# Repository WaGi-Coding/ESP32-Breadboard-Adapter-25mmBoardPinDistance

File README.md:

# ESP32-Breadboard-Adapter 25mm Board Pin Distance

Breadboard Adapter PCB to better fit an ESP32 DevKit onto your Breadboard. Has a Slot for a LED on GPIO2 and an OLED Screen (128x64).
The Pin Sequence is the same as from the ESP itself, just 2 Ground Pins got removed to save space.

It's designed for the "AZ-Delivery ESP32 DevKit C v4". If you have another Board, check the Pin mid distance, it should be 25mm, also check the Pinout of the mentioned Board.

You can DIRECTLY [ORDER FROM AISLER.NET HERE](https://aisler.net/p/QFYZRXHC) for very cheap. Here is also a 10€ Coupon Code (works atm [Jul. 10th 2022]): uCnet
You can also upload the files to some other PCB Manufacturer for sure.

### You need:
 - 2x 18Pin Male Header
 - 2x 19Pin Female Header (Hard to find, i cut 40 Pin Headers because they are cheap and easy to get)
 - (optional) I2C OLED Module (128x64 or something fitting ^^) [GND, 5V, SCL, SDA]
 - (optional) A LED (5mm or smaller diameter) + Resistor Connected to GPIO2

Made with KiCad

PS: It's a 1.6mm thick, 4 Layer PCB with throughhole Vias

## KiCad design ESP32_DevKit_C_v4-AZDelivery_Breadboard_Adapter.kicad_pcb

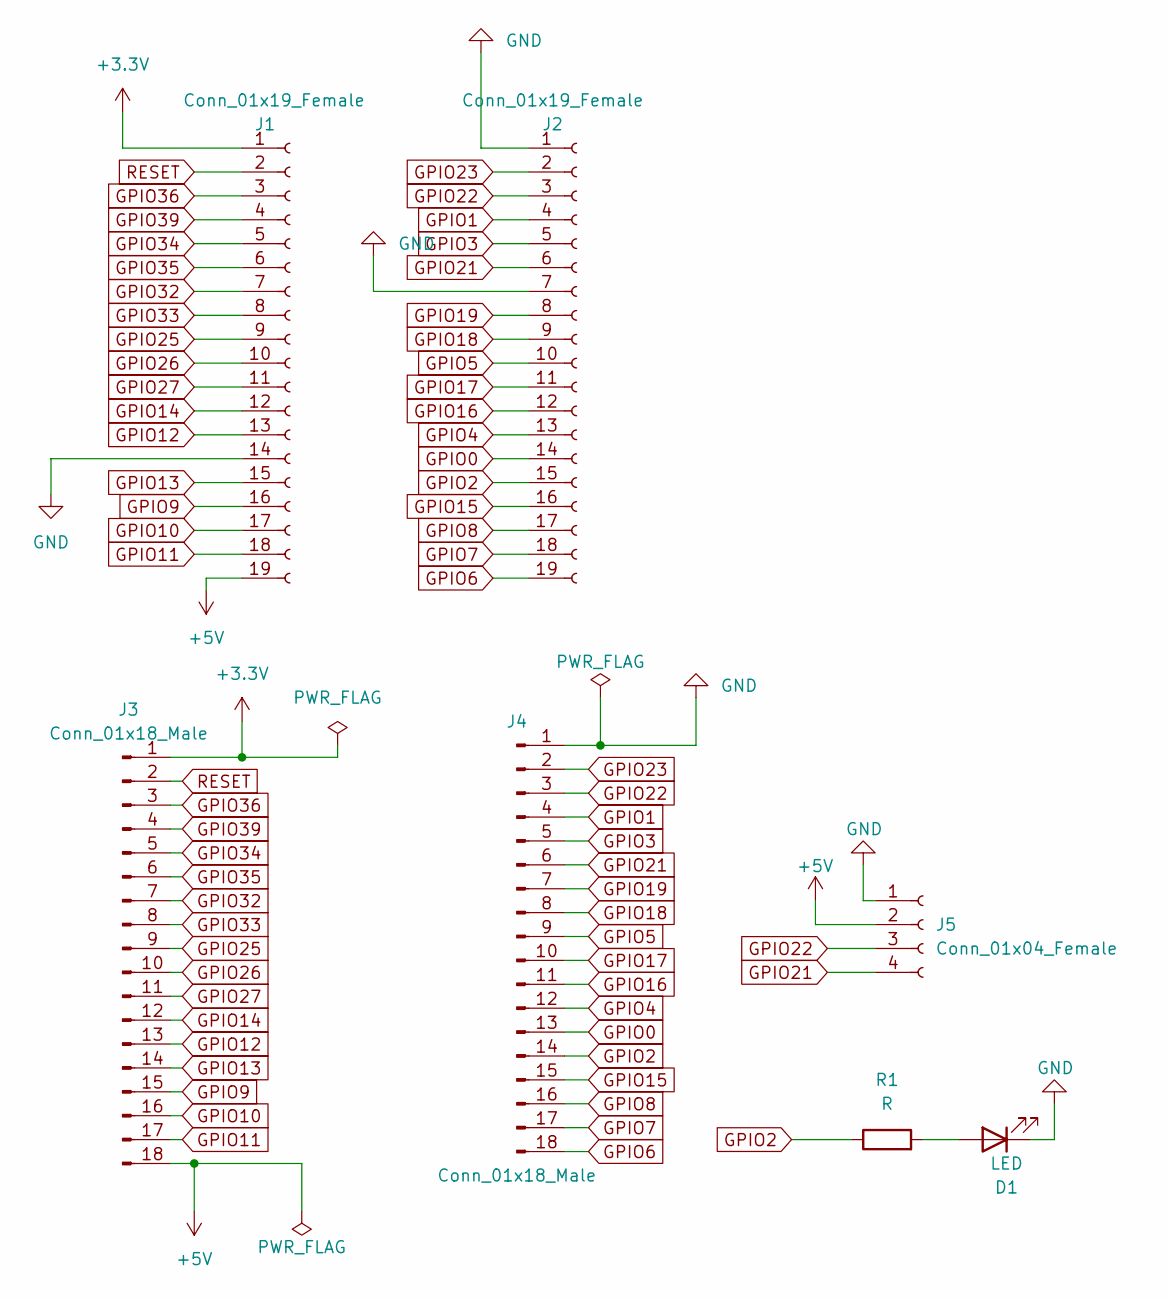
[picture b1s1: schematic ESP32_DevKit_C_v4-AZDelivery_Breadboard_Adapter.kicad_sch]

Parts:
D1: LED; LED_D5.0mm
J1, J2: Conn_01x19_Female; PinHeader_1x19_P2.54mm_Vertical
J3, J4: Conn_01x18_Male; PinHeader_1x18_P2.54mm_Vertical
J5: Conn_01x04_Female; PinHeader_1x04_P2.54mm_Vertical
R1: R; R_Axial_DIN0207_L6.3mm_D2.5mm_P7.62mm_Horizontal

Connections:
+3.3V: J1.1, J3.1
+5V: J1.19, J3.18, J5.2
GND: D1.1 (K), J1.14, J2.1, J2.7, J4.1, J5.1
GPIO0: J2.14, J4.13
GPIO1: J2.4, J4.4
GPIO2: J2.15, J4.14, R1.1
GPIO3: J2.5, J4.5
GPIO4: J2.13, J4.12
GPIO5: J2.10, J4.9
GPIO6: J2.19, J4.18
GPIO7: J2.18, J4.17
GPIO8: J2.17, J4.16
GPIO9: J1.16, J3.15
GPIO10: J1.17, J3.16
GPIO11: J1.18, J3.17
GPIO12: J1.13, J3.13
GPIO13: J1.15, J3.14
GPIO14: J1.12, J3.12
GPIO15: J2.16, J4.15
GPIO16: J2.12, J4.11
GPIO17: J2.11, J4.10
GPIO18: J2.9, J4.8
GPIO19: J2.8, J4.7
GPIO21: J2.6, J4.6, J5.4
GPIO22: J2.3, J4.3, J5.3
GPIO23: J2.2, J4.2
GPIO25: J1.9, J3.9
GPIO26: J1.10, J3.10
GPIO27: J1.11, J3.11
GPIO32: J1.7, J3.7
GPIO33: J1.8, J3.8
GPIO34: J1.5, J3.5
GPIO35: J1.6, J3.6
GPIO36: J1.3, J3.3
GPIO39: J1.4, J3.4
unnamed: D1.2 (A), R1.2
RESET: J1.2, J3.2

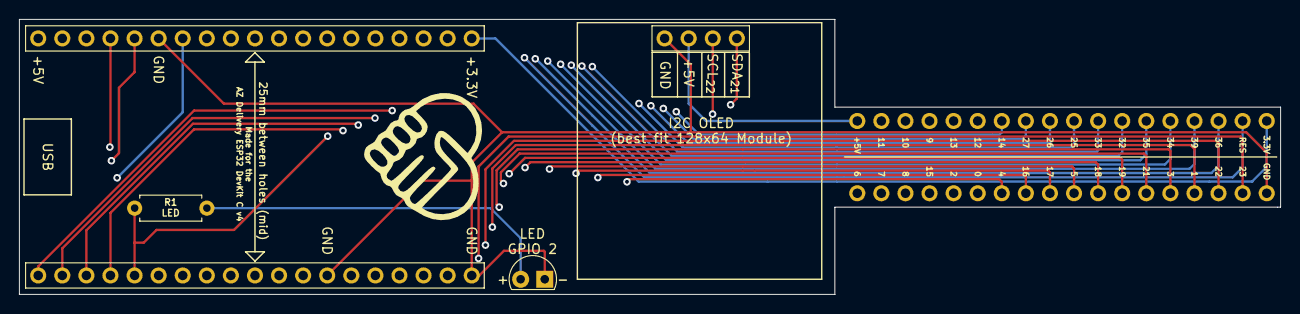
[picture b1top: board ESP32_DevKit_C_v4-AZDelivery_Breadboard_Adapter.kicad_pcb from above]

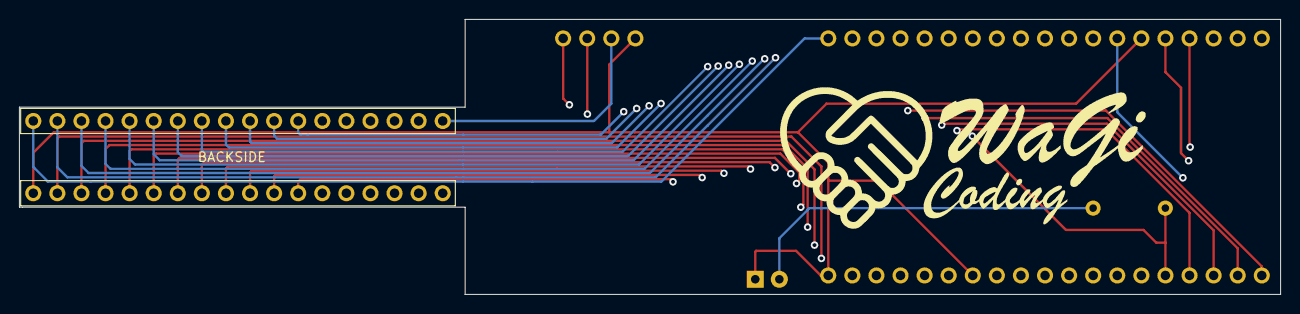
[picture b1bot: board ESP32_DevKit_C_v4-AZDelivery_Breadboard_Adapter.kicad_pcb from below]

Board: 4 copper layers, 133.0 x 29.0 mm, 7 parts (2 on the bottom side), 37 nets.

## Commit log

2022-07-11 Added coupon code
2022-07-11 color
